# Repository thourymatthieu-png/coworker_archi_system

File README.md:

# coworker_archi_system

Équipe d'agents IA experts (architecte système, exigences, logiciel, hardware, critique, cohérence, vérificateur de sources) pour mener des projets embarqués (électronique et logiciel) en cycle en V.

Point d'entrée : `CLAUDE.md` (charte). Agents : `.claude/agents/`. Procédures (skills) : `.claude/skills/`. Méthode : `framework/` (règles, portes, listes de contrôle, gabarits). Savoir-faire optionnel par outil ou fabricant : `modules/`. Projets : `projets/<nom>/`.

## Démarrer un projet

1. **Ouvrir Claude Code sur ce dépôt** (branche `main`, nouvelle session pour que les agents et les skills soient chargés). La session principale tient le rôle d'architecte : c'est à elle que vous parlez.
2. **Créer le projet** : taper `/nouveau-projet <nom>`. Les gabarits sont copiés dans `projets/<nom>/` et l'architecte remplit le profil (`projet.md`).
3. **Décrire ses scénarios** : l'architecte pose les questions (cas nominal, dégradés, d'échec, mise en service) et rédige `00-scenarios.md` avec vous. Préparer : ce que l'appareil doit faire, pour qui, dans quelles situations, et ce qui doit se passer quand quelque chose va mal.
4. **Porte « scénarios »** : `/porte scenarios` (l'architecte la lance lui-même quand la phase est prête). Relectures indépendantes, synthèse, puis votre accord explicite. Ensuite viennent les besoins, les exigences, l'architecture et la conception détaillée, chacun fermé par `/porte <phase>`.
5. **Changer un élément déjà validé** : `/modification <ID>`, jamais une retouche directe.
6. **Choix d'outils et de fabricant** (en général en architecture) : l'architecte présente les options ; votre choix est consigné en décision, inscrit dans `projet.md`, et active les modules correspondants (`modules/README.md`).

Vérifier un projet à tout moment : `python tools/check_traceability_V2.py projets/<nom> --phase <phase atteinte>`.

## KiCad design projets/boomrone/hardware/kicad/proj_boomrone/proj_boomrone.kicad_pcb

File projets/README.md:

# Projets

Un dossier par projet : `projets/<nom>/`.

Nouveau projet : copier le contenu de `framework/templates/` dans `projets/<nom>/`, puis lancer l'agent `architecte-systeme`. Le profil du projet (`projet.md`) déclare la cible, la chaîne d'outils et les modules actifs (`modules/README.md`) ; les scripts propres au projet vont dans `projets/<nom>/tools/`.

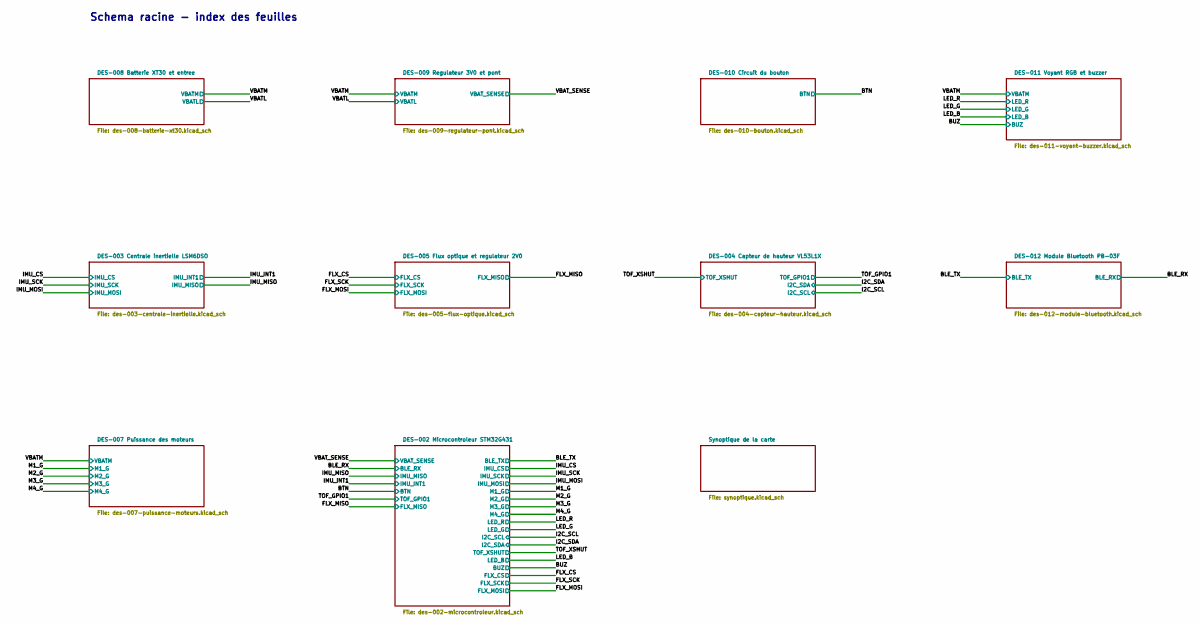
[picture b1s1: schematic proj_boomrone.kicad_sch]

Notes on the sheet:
Schema racine - index des feuilles

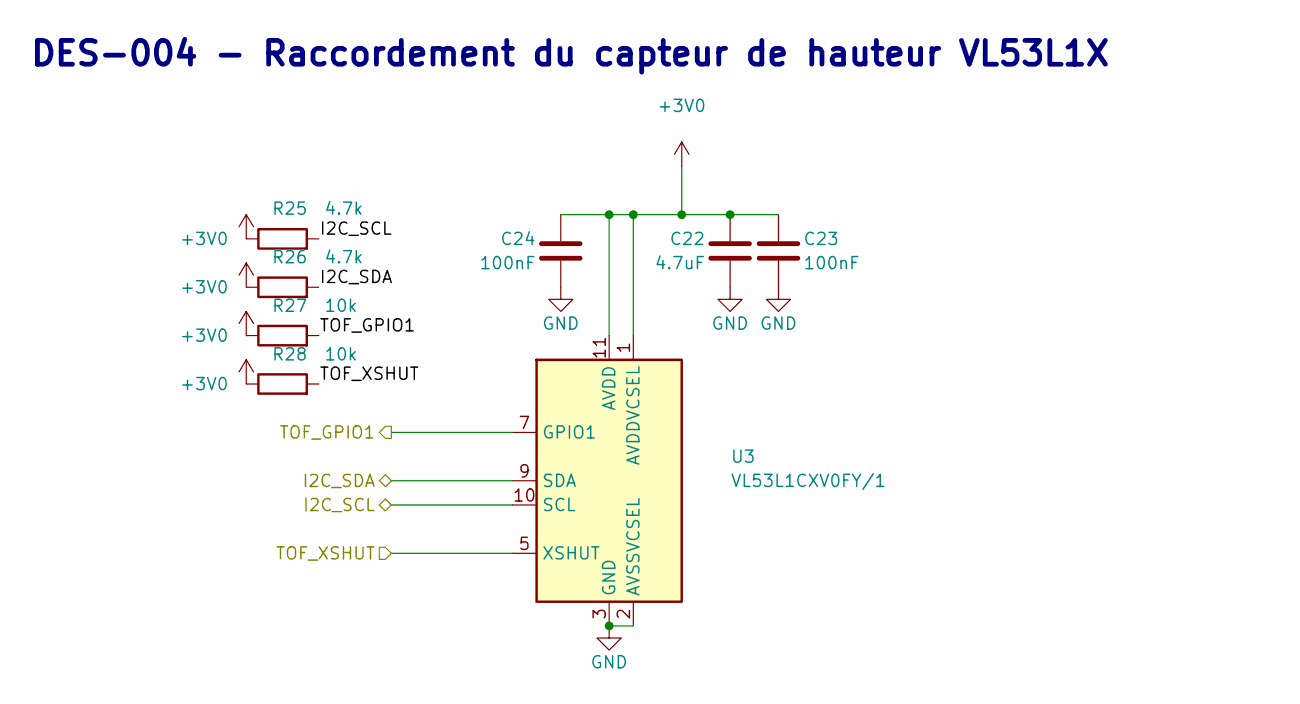
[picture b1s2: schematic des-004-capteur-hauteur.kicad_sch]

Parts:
C22: 4.7uF; C_0603_1608Metric
C23, C24: 100nF; C_0603_1608Metric
R25, R26: 4.7k; R_0603_1608Metric
R27, R28: 10k; R_0603_1608Metric
U3: VL53L1CXV0FY/1; ST_VL53L1x

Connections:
+3V0: C22.1, C23.1, C24.1, R25.1, R26.1, R27.1, R28.1, U3.1 (AVDDVCSEL), U3.11 (AVDD); also elsewhere on the board
/I2C_SCL: R25.2, U3.10 (SCL); also elsewhere on the board
/I2C_SDA: R26.2, U3.9 (SDA); also elsewhere on the board
/TOF_GPIO1: R27.2, U3.7 (GPIO1); also elsewhere on the board
/TOF_XSHUT: R28.2, U3.5 (XSHUT); also elsewhere on the board
GND: C22.2, C23.2, C24.2, U3.2 (AVSSVCSEL), U3.3 (GND), U3.4 (GND), U3.6 (GND), U3.12 (GND); also elsewhere on the board

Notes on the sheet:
DES-004 - Raccordement du capteur de hauteur VL53L1X

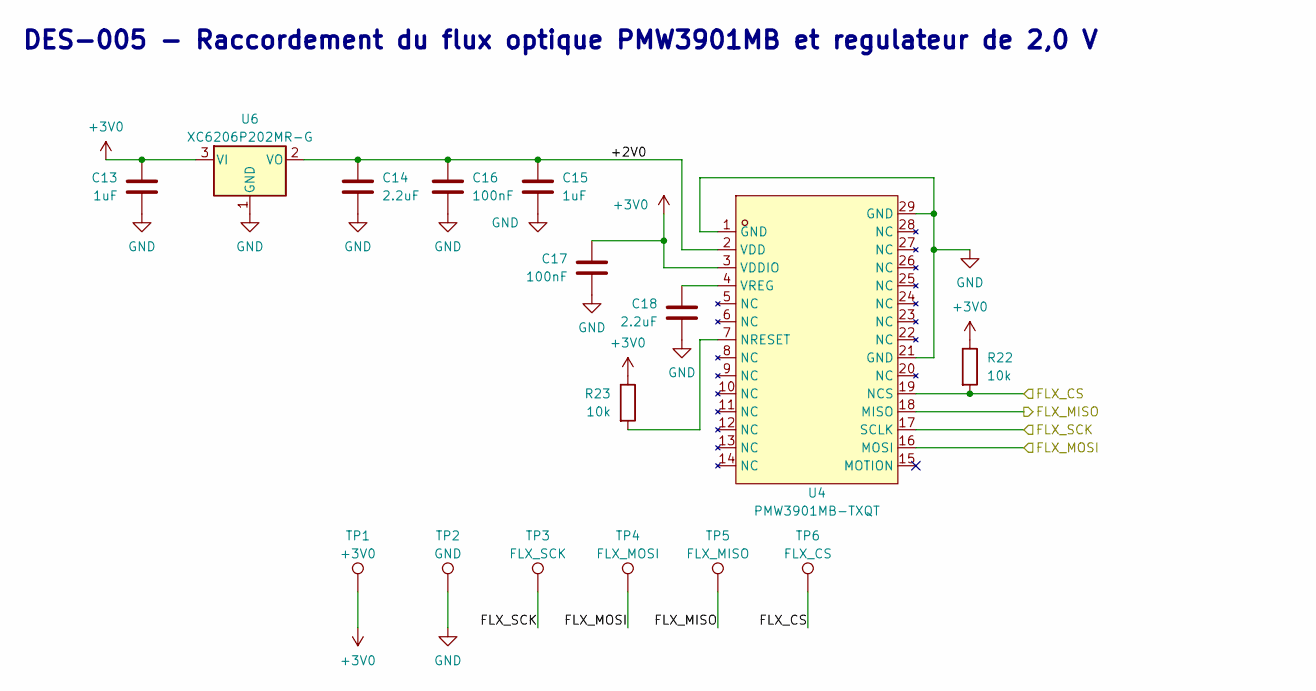
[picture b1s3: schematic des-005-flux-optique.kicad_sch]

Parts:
C13, C15: 1uF; C_0603_1608Metric
C14, C18: 2.2uF; C_0603_1608Metric
C16, C17: 100nF; C_0603_1608Metric
R22, R23: 10k; R_0603_1608Metric
TP1: +3V0; TestPoint_Pad_1.5x1.5mm
TP2: GND; TestPoint_Pad_1.5x1.5mm
TP3: FLX_SCK; TestPoint_Pad_1.5x1.5mm
TP4: FLX_MOSI; TestPoint_Pad_1.5x1.5mm
TP5: FLX_MISO; TestPoint_Pad_1.5x1.5mm
TP6: FLX_CS; TestPoint_Pad_1.5x1.5mm
U4: PMW3901MB-TXQT; COB-28_L6.0-W6.0-P0.65-TL-EP
U6: XC6206P202MR-G; SOT-23

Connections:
+3V0: C13.1, C17.1, R22.1, R23.1, TP1.1 (1_1), U4.3 (VDDIO), U6.3 (VI); also elsewhere on the board
/DES-005 Flux optique et regulateur 2V0/+2V0: C14.1, C15.1, C16.1, U4.2 (VDD), U6.2 (VO)
/FLX_CS: R22.2, TP6.1 (1_1), U4.19 (NCS); also elsewhere on the board
/FLX_MISO: TP5.1 (1_1), U4.18 (MISO); also elsewhere on the board
/FLX_MOSI: TP4.1 (1_1), U4.16 (MOSI); also elsewhere on the board
/FLX_SCK: TP3.1 (1_1), U4.17 (SCLK); also elsewhere on the board
GND: C13.2, C14.2, C15.2, C16.2, C17.2, C18.2, TP2.1 (1_1), U4.1 (GND), U4.21 (GND), U4.29 (GND), U6.1 (GND); also elsewhere on the board
unnamed: R23.2, U4.7 (NRESET)
unnamed: C18.1, U4.4 (VREG)

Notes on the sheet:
DES-005 - Raccordement du flux optique PMW3901MB et regulateur de 2,0 V

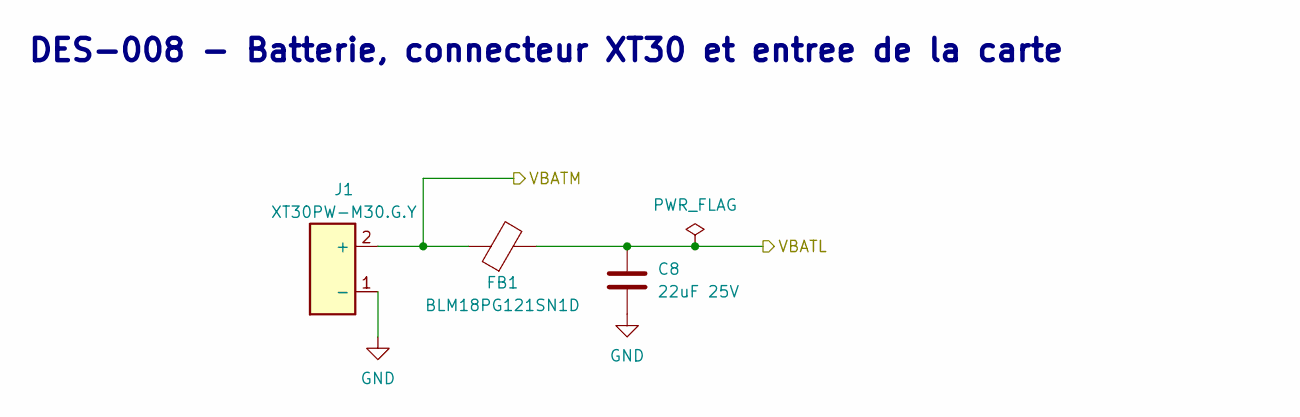
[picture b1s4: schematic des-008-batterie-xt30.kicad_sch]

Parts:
C8: 22uF 25V; C_1206_3216Metric
FB1: BLM18PG121SN1D; L_0603_1608Metric
J1: XT30PW-M30.G.Y; CONN-TH_XT30PW-M

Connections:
/VBATL: C8.1, FB1.2; also elsewhere on the board
/VBATM: FB1.1, J1.2 (+); also elsewhere on the board
GND: C8.2, J1.1 (-); also elsewhere on the board

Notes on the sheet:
DES-008 - Batterie, connecteur XT30 et entree de la carte

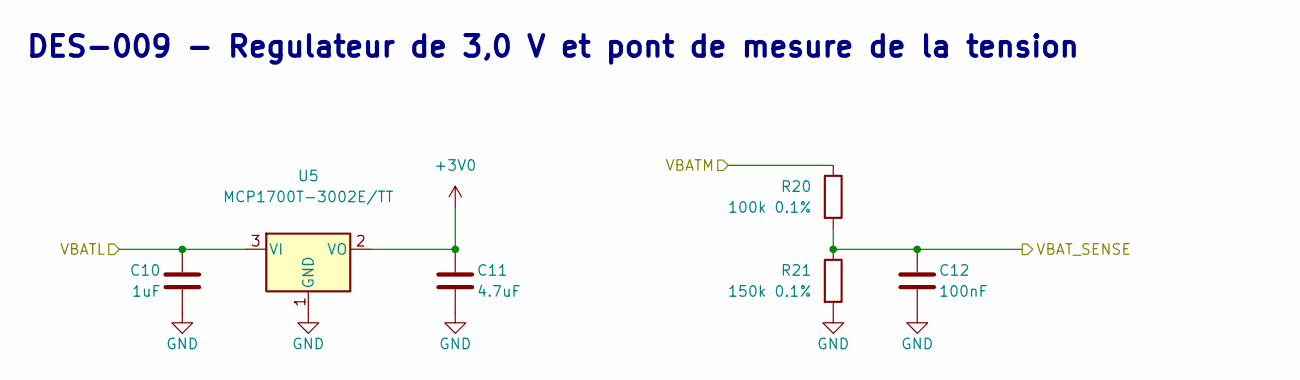
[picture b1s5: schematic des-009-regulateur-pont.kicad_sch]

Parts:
C10: 1uF; C_0603_1608Metric
C11: 4.7uF; C_0603_1608Metric
C12: 100nF; C_0603_1608Metric
R20: 100k 0.1%; R_0603_1608Metric
R21: 150k 0.1%; R_0603_1608Metric
U5: MCP1700T-3002E/TT; SOT-23

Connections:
+3V0: C11.1, U5.2 (VO); also elsewhere on the board
/VBATL: C10.1, U5.3 (VI); also elsewhere on the board
/VBATM: R20.1; also elsewhere on the board
/VBAT_SENSE: C12.1, R20.2, R21.1; also elsewhere on the board
GND: C10.2, C11.2, C12.2, R21.2, U5.1 (GND); also elsewhere on the board

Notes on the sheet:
DES-009 - Regulateur de 3,0 V et pont de mesure de la tension

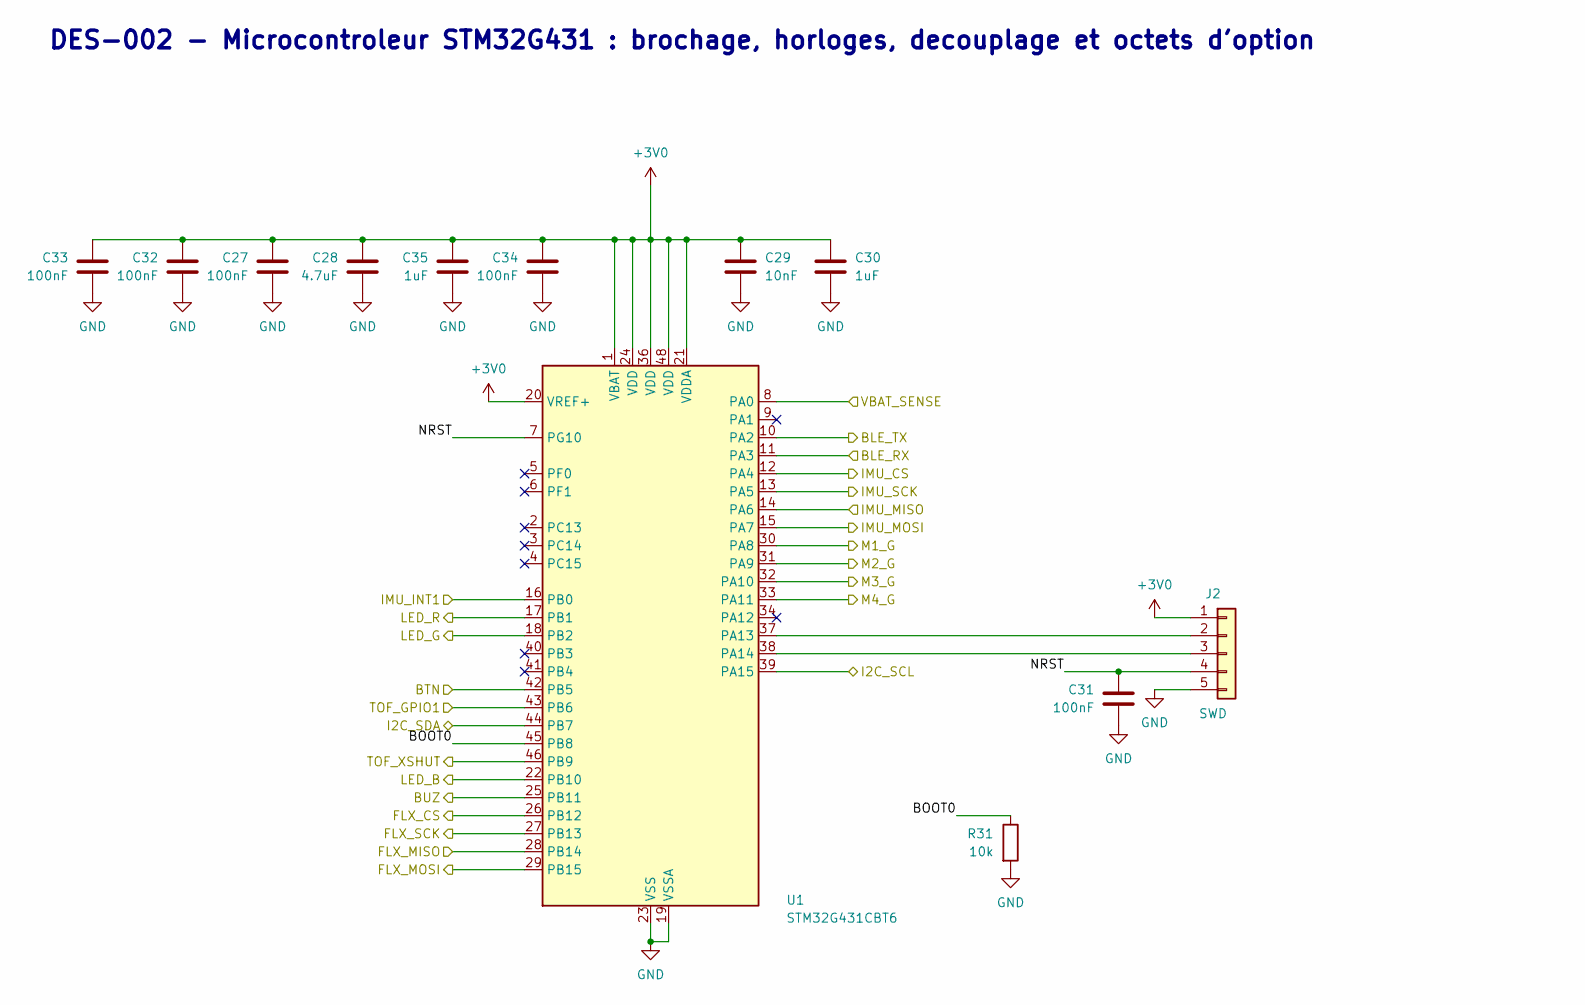
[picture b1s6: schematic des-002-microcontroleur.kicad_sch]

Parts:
C27, C31, C32, C33, C34: 100nF; C_0603_1608Metric
C28: 4.7uF; C_0603_1608Metric
C29: 10nF; C_0603_1608Metric
C30, C35: 1uF; C_0603_1608Metric
J2: SWD; PinHeader_1x05_P2.54mm_Vertical
R31: 10k; R_0603_1608Metric
U1: STM32G431CBT6; LQFP-48_7x7mm_P0.5mm

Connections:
+3V0: C27.1, C28.1, C29.1, C30.1, C32.1, C33.1, C34.1, C35.1, J2.1, U1.1 (VBAT), U1.20 (VREF+), U1.21 (VDDA), U1.24 (VDD), U1.36 (VDD), U1.48 (VDD); also elsewhere on the board
/BLE_RX: U1.11 (PA3); also elsewhere on the board
/BLE_TX: U1.10 (PA2); also elsewhere on the board
/BTN: U1.42 (PB5); also elsewhere on the board
/BUZ: U1.25 (PB11); also elsewhere on the board
/DES-002 Microcontroleur STM32G431/BOOT0: R31.1, U1.45 (PB8)
/DES-002 Microcontroleur STM32G431/NRST: C31.1, J2.4, U1.7 (PG10)
/FLX_CS: U1.26 (PB12); also elsewhere on the board
/FLX_MISO: U1.28 (PB14); also elsewhere on the board
/FLX_MOSI: U1.29 (PB15); also elsewhere on the board
/FLX_SCK: U1.27 (PB13); also elsewhere on the board
/I2C_SCL: U1.39 (PA15); also elsewhere on the board
/I2C_SDA: U1.44 (PB7); also elsewhere on the board
/IMU_CS: U1.12 (PA4); also elsewhere on the board
/IMU_INT1: U1.16 (PB0); also elsewhere on the board
/IMU_MISO: U1.14 (PA6); also elsewhere on the board
/IMU_MOSI: U1.15 (PA7); also elsewhere on the board
/IMU_SCK: U1.13 (PA5); also elsewhere on the board
/LED_B: U1.22 (PB10); also elsewhere on the board
/LED_G: U1.18 (PB2); also elsewhere on the board
/LED_R: U1.17 (PB1); also elsewhere on the board
/M1_G: U1.30 (PA8); also elsewhere on the board
/M2_G: U1.31 (PA9); also elsewhere on the board
/M3_G: U1.32 (PA10); also elsewhere on the board
/M4_G: U1.33 (PA11); also elsewhere on the board
/TOF_GPIO1: U1.43 (PB6); also elsewhere on the board
/TOF_XSHUT: U1.46 (PB9); also elsewhere on the board
/VBAT_SENSE: U1.8 (PA0); also elsewhere on the board
GND: C27.2, C28.2, C29.2, C30.2, C31.2, C32.2, C33.2, C34.2, C35.2, J2.5, R31.2, U1.19 (VSSA), U1.23 (VSS), U1.35 (VSS), U1.47 (VSS); also elsewhere on the board
unnamed: J2.2, U1.37 (PA13)
unnamed: J2.3, U1.38 (PA14)

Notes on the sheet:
DES-002 - Microcontroleur STM32G431 : brochage, horloges, decouplage et octets d'option

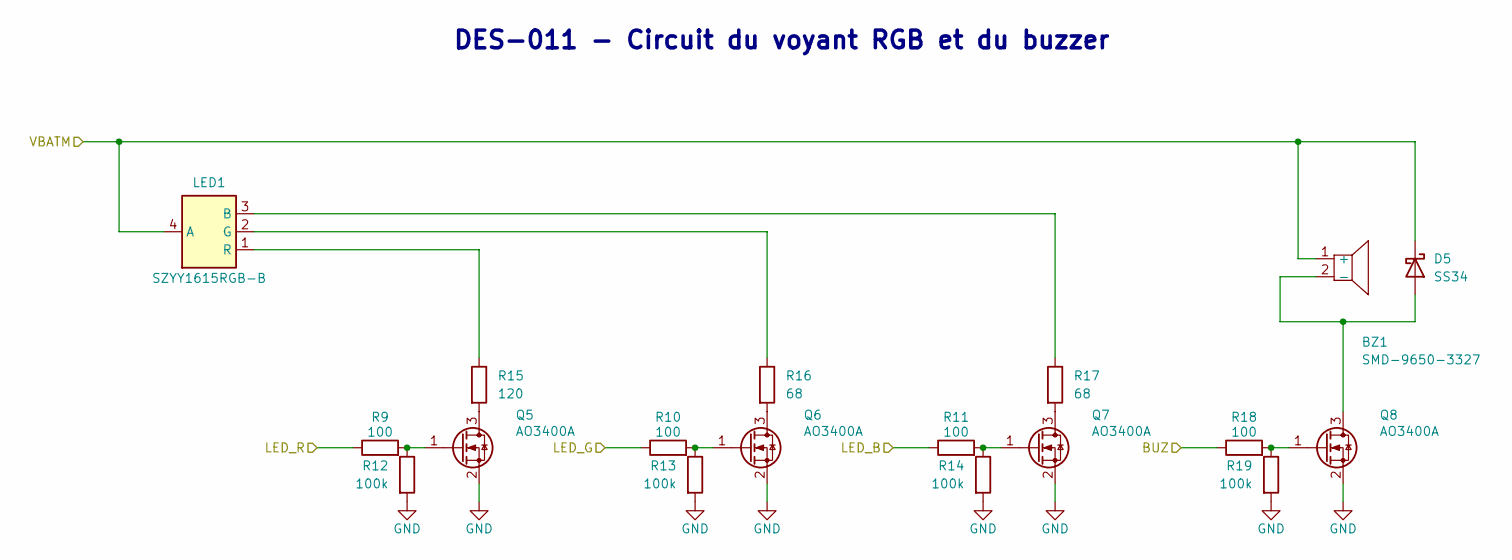
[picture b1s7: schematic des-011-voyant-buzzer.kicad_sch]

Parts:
BZ1: SMD-9650-3327; BUZ-SMD_L9.0-W9.0_SMD-0955-42-27
D5: SS34; D_SMA
LED1: SZYY1615RGB-B; LED-SMD_4P-L1.6-W1.5-TR-1
Q5, Q6, Q7, Q8: AO3400A; SOT-23
R9, R10, R11, R18: 100; R_0603_1608Metric
R12, R13, R14, R19: 100k; R_0603_1608Metric
R15: 120; R_0603_1608Metric
R16, R17: 68; R_0603_1608Metric

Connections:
/BUZ: R18.1; also elsewhere on the board
/LED_B: R11.1; also elsewhere on the board
/LED_G: R10.1; also elsewhere on the board
/LED_R: R9.1; also elsewhere on the board
/VBATM: BZ1.1 (+), D5.1 (K), LED1.4 (A); also elsewhere on the board
GND: Q5.2 (S), Q6.2 (S), Q7.2 (S), Q8.2 (S), R12.2, R13.2, R14.2, R19.2; also elsewhere on the board
unnamed: BZ1.2 (-), D5.2 (A), Q8.3 (D)
unnamed: LED1.3 (B), R17.1
unnamed: LED1.2 (G), R16.1
unnamed: LED1.1 (R), R15.1
unnamed: Q5.3 (D), R15.2
unnamed: Q5.1 (G), R9.2, R12.1
unnamed: Q6.3 (D), R16.2
unnamed: Q6.1 (G), R10.2, R13.1
unnamed: Q7.3 (D), R17.2
unnamed: Q7.1 (G), R11.2, R14.1
unnamed: Q8.1 (G), R18.2, R19.1

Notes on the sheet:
DES-011 - Circuit du voyant RGB et du buzzer

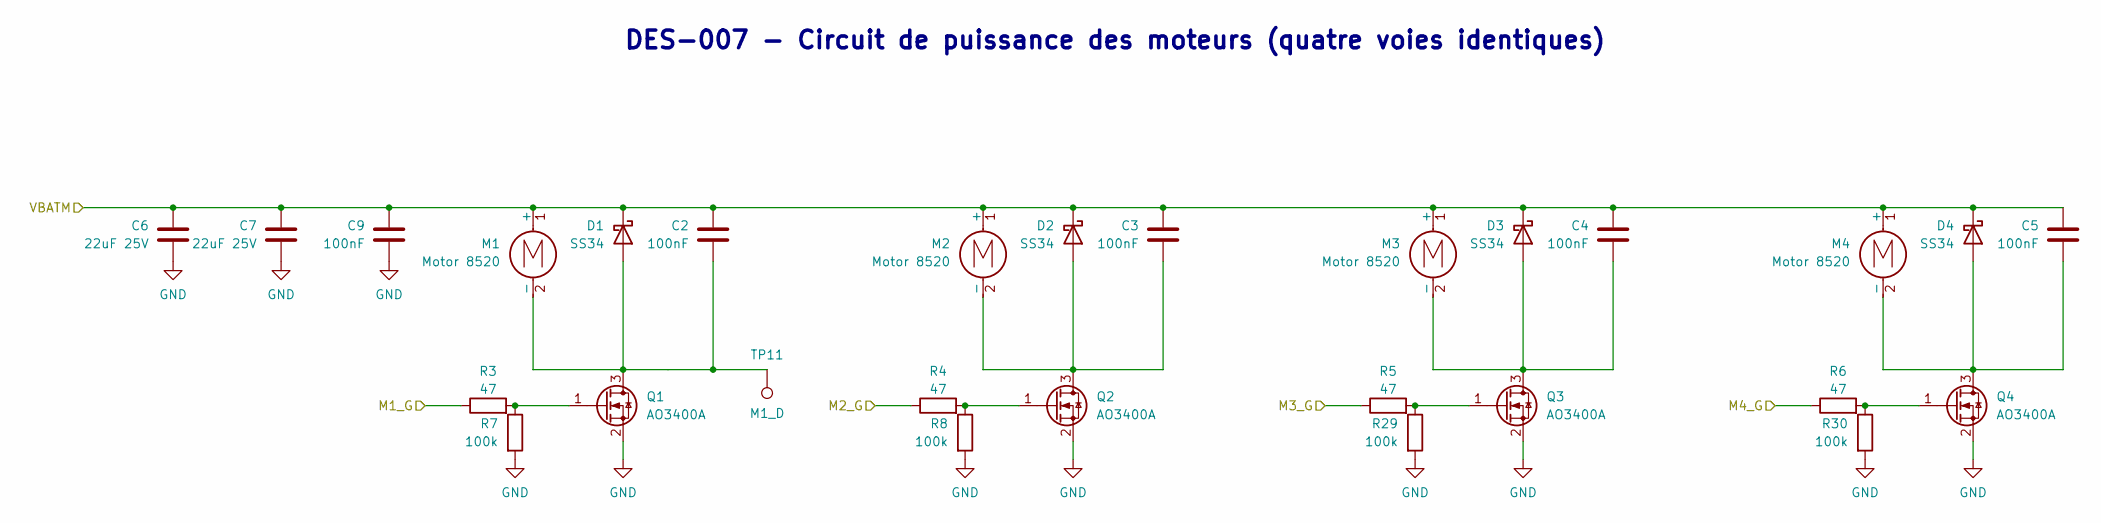
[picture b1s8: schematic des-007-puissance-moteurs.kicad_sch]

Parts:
C2, C3, C4, C5, C9: 100nF; C_0603_1608Metric
C6, C7: 22uF 25V; C_1206_3216Metric
D1, D2, D3, D4: SS34; D_SMA
M1, M2, M3, M4: Motor 8520; Motor_8520_2Pads_P5.8mm
Q1, Q2, Q3, Q4: AO3400A; SOT-23
R3, R4, R5, R6: 47; R_0603_1608Metric
R7, R8, R29, R30: 100k; R_0603_1608Metric
TP11: M1_D; TestPoint_Pad_1.5x1.5mm

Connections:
/M1_G: R3.1; also elsewhere on the board
/M2_G: R4.1; also elsewhere on the board
/M3_G: R5.1; also elsewhere on the board
/M4_G: R6.1; also elsewhere on the board
/VBATM: C2.1, C3.1, C4.1, C5.1, C6.1, C7.1, C9.1, D1.1 (K), D2.1 (K), D3.1 (K), D4.1 (K), M1.1 (+), M2.1 (+), M3.1 (+), M4.1 (+); also elsewhere on the board
GND: C6.2, C7.2, C9.2, Q1.2 (S), Q2.2 (S), Q3.2 (S), Q4.2 (S), R7.2, R8.2, R29.2, R30.2; also elsewhere on the board
unnamed: C2.2, D1.2 (A), M1.2 (-), Q1.3 (D), TP11.1 (1_1)
unnamed: C3.2, D2.2 (A), M2.2 (-), Q2.3 (D)
unnamed: C4.2, D3.2 (A), M3.2 (-), Q3.3 (D)
unnamed: C5.2, D4.2 (A), M4.2 (-), Q4.3 (D)
unnamed: Q1.1 (G), R3.2, R7.1
unnamed: Q2.1 (G), R4.2, R8.1
unnamed: Q3.1 (G), R5.2, R29.1
unnamed: Q4.1 (G), R6.2, R30.1

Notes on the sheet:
DES-007 - Circuit de puissance des moteurs (quatre voies identiques)

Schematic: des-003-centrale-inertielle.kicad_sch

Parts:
C19, C20: 100nF; C_0603_1608Metric
C21: 10uF; C_0603_1608Metric
R24: 10k; R_0603_1608Metric
U2: LSM6DSOTR; LGA-14_3x2.5mm_P0.5mm_LayoutBorder3x4y

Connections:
+3V0: C19.1, C20.1, C21.1, R24.1, U2.5 (VDDIO), U2.8 (VDD); also elsewhere on the board
/IMU_CS: R24.2, U2.12 (CS); also elsewhere on the board
/IMU_INT1: U2.4 (INT1); also elsewhere on the board
/IMU_MISO: U2.1 (SDO/SA0); also elsewhere on the board
/IMU_MOSI: U2.14 (SDA); also elsewhere on the board
/IMU_SCK: U2.13 (SCL); also elsewhere on the board
GND: C19.2, C20.2, C21.2, U2.2 (SDx), U2.3 (SCx), U2.6 (GND), U2.7 (GND); also elsewhere on the board

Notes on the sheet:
DES-003 - Raccordement de la centrale inertielle LSM6DSO

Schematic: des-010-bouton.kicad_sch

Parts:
C1: 10nF; C_0603_1608Metric
R1: 1k; R_0603_1608Metric
R2: 10k; R_0603_1608Metric
SW1: TS-1088-AR02016; SW_SPST_TS-1088-xR020

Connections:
+3V0: R2.1; also elsewhere on the board
/BTN: C1.1, R1.2, R2.2; also elsewhere on the board
GND: C1.2, SW1.1; also elsewhere on the board
unnamed: R1.1, SW1.2

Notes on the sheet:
DES-010 - Circuit du bouton

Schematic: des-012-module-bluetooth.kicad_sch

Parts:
C36: 10uF; C_0603_1608Metric
C37: 100nF; C_0603_1608Metric
TP7: +3V0; TestPoint_Pad_1.5x1.5mm
TP8: GND; TestPoint_Pad_1.5x1.5mm
TP9: BLE_TX; TestPoint_Pad_1.5x1.5mm
TP10: BLE_RX; TestPoint_Pad_1.5x1.5mm
U7: PB-03F; BULETM-SMD_PB-03F

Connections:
+3V0: C36.1, C37.1, TP7.1 (1_1), U7.8 (VDD); also elsewhere on the board
/BLE_RX: TP10.1 (1_1), U7.22 (P9); also elsewhere on the board
/BLE_TX: TP9.1 (1_1), U7.21 (P10); also elsewhere on the board
GND: C36.2, C37.2, TP8.1 (1_1), U7.15 (GND); also elsewhere on the board

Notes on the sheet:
DES-012 - Raccordement du module Bluetooth PB-03F

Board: 2 copper layers, 107 parts (0 on the bottom side), 56 nets, no tracks yet.

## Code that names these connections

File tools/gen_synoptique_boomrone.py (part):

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dot(900, 195, C["bat"])
line([(900, 195), (900, 330)], C["bat"], 2.4)
box(840, 330, 120, 70, "Pont diviseur", ["100 kΩ / 150 kΩ", "DES-009"], tw=13)
t(970, 420, "VBAT_SENSE vers PA0 (ADC)", C["sig"], 11)
t(330, 330, "Masse unique : plan plein", C["gnd"], 12, bold=True)
t(330, 348, "Points d'essai : +3V0, +2V0, VBATM, VBATL, GND ×2", C["gnd"], 11)
t(330, 364, "Aucune protection contre l'inversion ni la surintensité", C["warn"], 11)
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# voyant + buzzer
line([(325, 1190), (870, 1190)], C["bat"], 3.4)
box(360, 1030, 280, 140, "LED1  voyant RGB SZYY1615RGB-B",
    ["anode commune sur VBATM", "Q5, Q6, Q7 ← LED_R/G/B (PB1, PB2, PB10)",
     "120 Ω rouge, 68 Ω vert et bleu", "15 à 18 mA par couleur · DES-011"], tw=13)
box(670, 1030, 200, 140, "BZ1  buzzer actif",
    ["SMD-9650-3327 · 3,3 V · 30 mA", "80 dB à 10 cm · 2 700 Hz", "Q8 ← BUZ (PB11)", "DES-011"], tw=13)
line([(500, 1190), (500, 1170)], C["bat"], 2.6)
line([(770, 1190), (770, 1170)], C["bat"], 2.6)
dot(500, 1190, C["bat"])
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     "cycle 1 kHz · machine à états unique (18 états)",
     "chien de garde matériel de 100 ms · BOR",
     "SPI1 · SPI2 · I²C1 · USART2 · TIM1 · ADC1",
     "SWD (PA13, PA14) · NRST · BOOT0 (PB8)",
     "DES-002 · découplage de VDD et VDDA"], fill="#eff6ff", tw=17)
line([(1130, 259), (1160, 259)], C["l3"], 3.4)
t(1165, 428, "Sorties de TIM1 (PA8 à PA11) vers les grilles Q1 à Q4 : bloc ACTIONNEURS", C["sig"], 11)
# tronc de signaux à droite
line([(1520, 300), (1535, 300), (1535, 1075)], C["sig"], 2.6)
dot(1535, 300, C["sig"])

zone(1150, 445, 390, 335, "CAPTEURS (face basse)", C["sig"])
sens = [(470, "U2  LSM6DSO · centrale inertielle", ["accéléromètre + gyroscope 3 axes", "SPI1 PA4–PA7 (5,3 MHz) · INT1 PB0 · DES-003"], C["sig"]),
        (555, "U3  VL53L1CX · hauteur par temps de vol", ["fiable dès 40 mm · I²C1 PA15/PB7", "XSHUT PB9 · GPIO1 PB6 · DES-004"], C["sig"]),
        (640, "U4  PMW3901MB · flux optique", ["dérive horizontale · SPI2 PB12–PB15 (1,33 MHz)", "VDD 2,0 V · VDDIO 3,0 V · lentille collée · DES-005"], C["sig"])]
for y, ti, su, c in sens:
    box(1170, y, 330, 70, ti, su, tw=13)
    line([(1500, y + 35), (1535, y + 35)], c, 2.4)
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
zone(1150, 795, 390, 190, "RADIO", C["ser"])
box(1170, 825, 330, 90, "U7  PB-03F (Ai-Thinker)",
    ["PHY6252 · Bluetooth 5.2 · antenne sur le module", "USART2 : PA2 → RXD (P10), TXD (P9) → PA3", "115 200 bauds · DES-012"], tw=14)
line([(1500, 870), (1542, 870), (1542, 350), (1520, 350)], C["ser"], 2.6, arrow="ser")
t(1170, 940, "Microprogramme d'origine, aucune commande envoyée :", C["warn"], 11)
t(1170, 956, "à essayer seul avant la commande (DOU-200).", C["warn"], 11)
t(1170, 972, "Antenne en dépassement du bord de carte (DOU-204).", C["warn"], 11)

zone(1150, 1000, 390, 215, "INTERFACES LOCALES", "#9333ea")
box(1170, 1030, 330, 60, "SW1  bouton", ["PB5 · rappel 10 kΩ · RC antirebond · DES-010"], tw=13)
box(1170, 1105, 330, 60, "J2  en-tête SWD 1×5", ["VTref · SWDIO (PA13) · SWCLK (PA14) · GND · NRST"], tw=13)
line([(1500, 1060), (1535, 1060)], C["sig"], 2.4)
dot(1535, 1060, C["sig"])
line([(1500, 1135), (1548, 1135), (1548, 380), (1520, 380)], C["gnd"], 2.4, dash="6 4", arrow="gnd")
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                       "Carte 40 × 35 mm, 1,0 mm, double face."]):
    t(1595, 552 + i * 19, "• " + s, size=12)
t(1595, 630, "Points d'essai (TP1 à TP11)", size=13, bold=True)
for i, s in enumerate(["+3V0, +2V0, VBATM, VBATL, GND ×2,", "M1_D, BLE_TX, BLE_RX, TOF_GPIO1,", "plus 6 plots de repli du flux optique."]):
    t(1595, 652 + i * 19, s, size=12)
t(1595, 730, "Un diagramme par bloc : feuilles DES-002 à DES-012", size=12, col="#4b5563")
t(1595, 748, "du projet KiCad (DES-006 : mécanique, hors carte).", size=12, col="#4b5563")
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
